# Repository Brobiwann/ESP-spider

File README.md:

# ESP-spider

The ESP-Spider is a quadruped robot inspired by the miniKame (https://github.com/JavierIH/miniKame) . Like the miniKame, it uses sinusoidal functions to control servo positions,
but the design and code were developed independently to better learn the process.
Currently, the robot performs three main actions: move forward, turn right, and turn left, with plans to add more functions in the future as I learn.

# Electronics

The robot features a custom PCB (gerber files and KiCad project are in the repository) with:

  - ESP32 module
  - PCA9685 for PWM control of servos
    
Additional components:

  - 8x MG92B servos
  - 3x 18650 cells
  - 3S BMS 40A 12V with balance charging
  - DFR0753 (DC-DC Buck Converter 6–14V to 5V/8A)
  - Adafruit 1.2" 8x8 LED Matrix Backpack
  - 2.1mmx5.5mm DC Power Jack (Female)
  - Mini 5V fan (20mmx10mm)

# 3D Printing

All STL, Soliworks and STEP files are provided in the repository.
The design is optimized for resin printing and also uses 4x 11mm ball bearings to support the robot weight.
The assembly is completed using M3 and M2 bolts and nuts

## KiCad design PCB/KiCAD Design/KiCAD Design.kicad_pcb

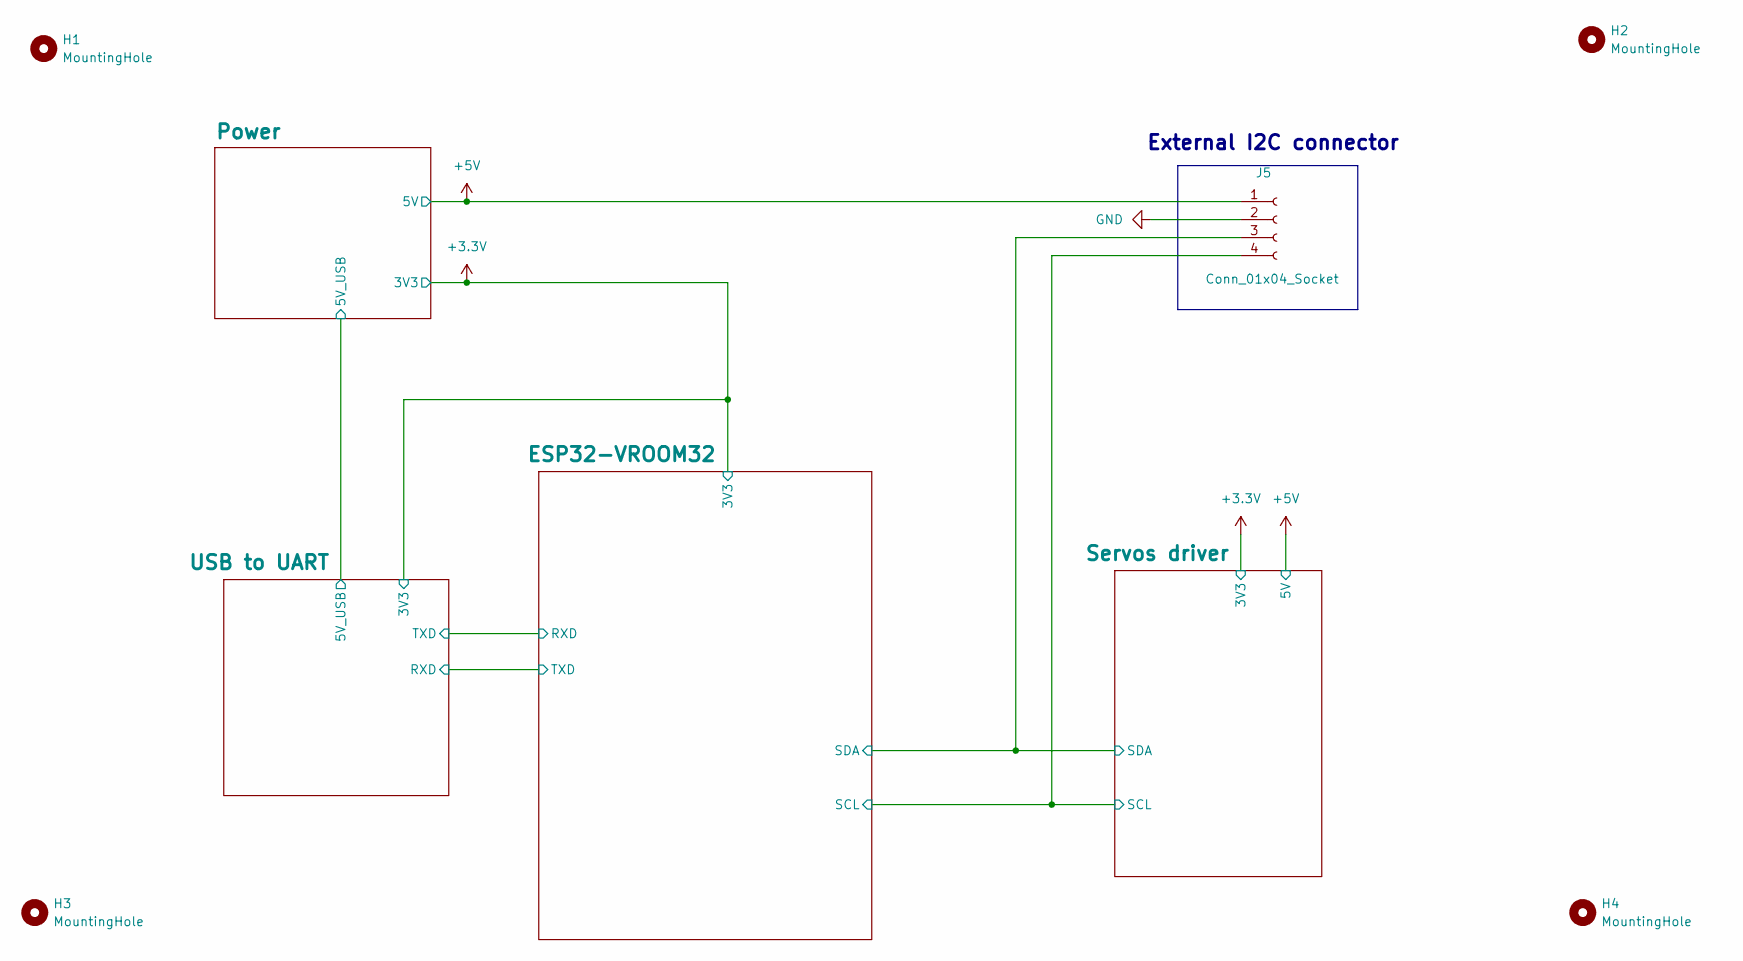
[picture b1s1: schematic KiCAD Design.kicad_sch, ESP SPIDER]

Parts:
H1, H2, H3, H4: MountingHole; MountingHole_2.2mm_M2
J5: Conn_01x04_Socket; JST_PH_B4B-PH-K_1x04_P2.00mm_Vertical; LCSC C131334

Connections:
+5V: J5.1; also elsewhere on the board
/ESP32-VROOM32/SCL: J5.4; also elsewhere on the board
/ESP32-VROOM32/SDA: J5.3; also elsewhere on the board
GND: J5.2; also elsewhere on the board

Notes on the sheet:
External I2C connector

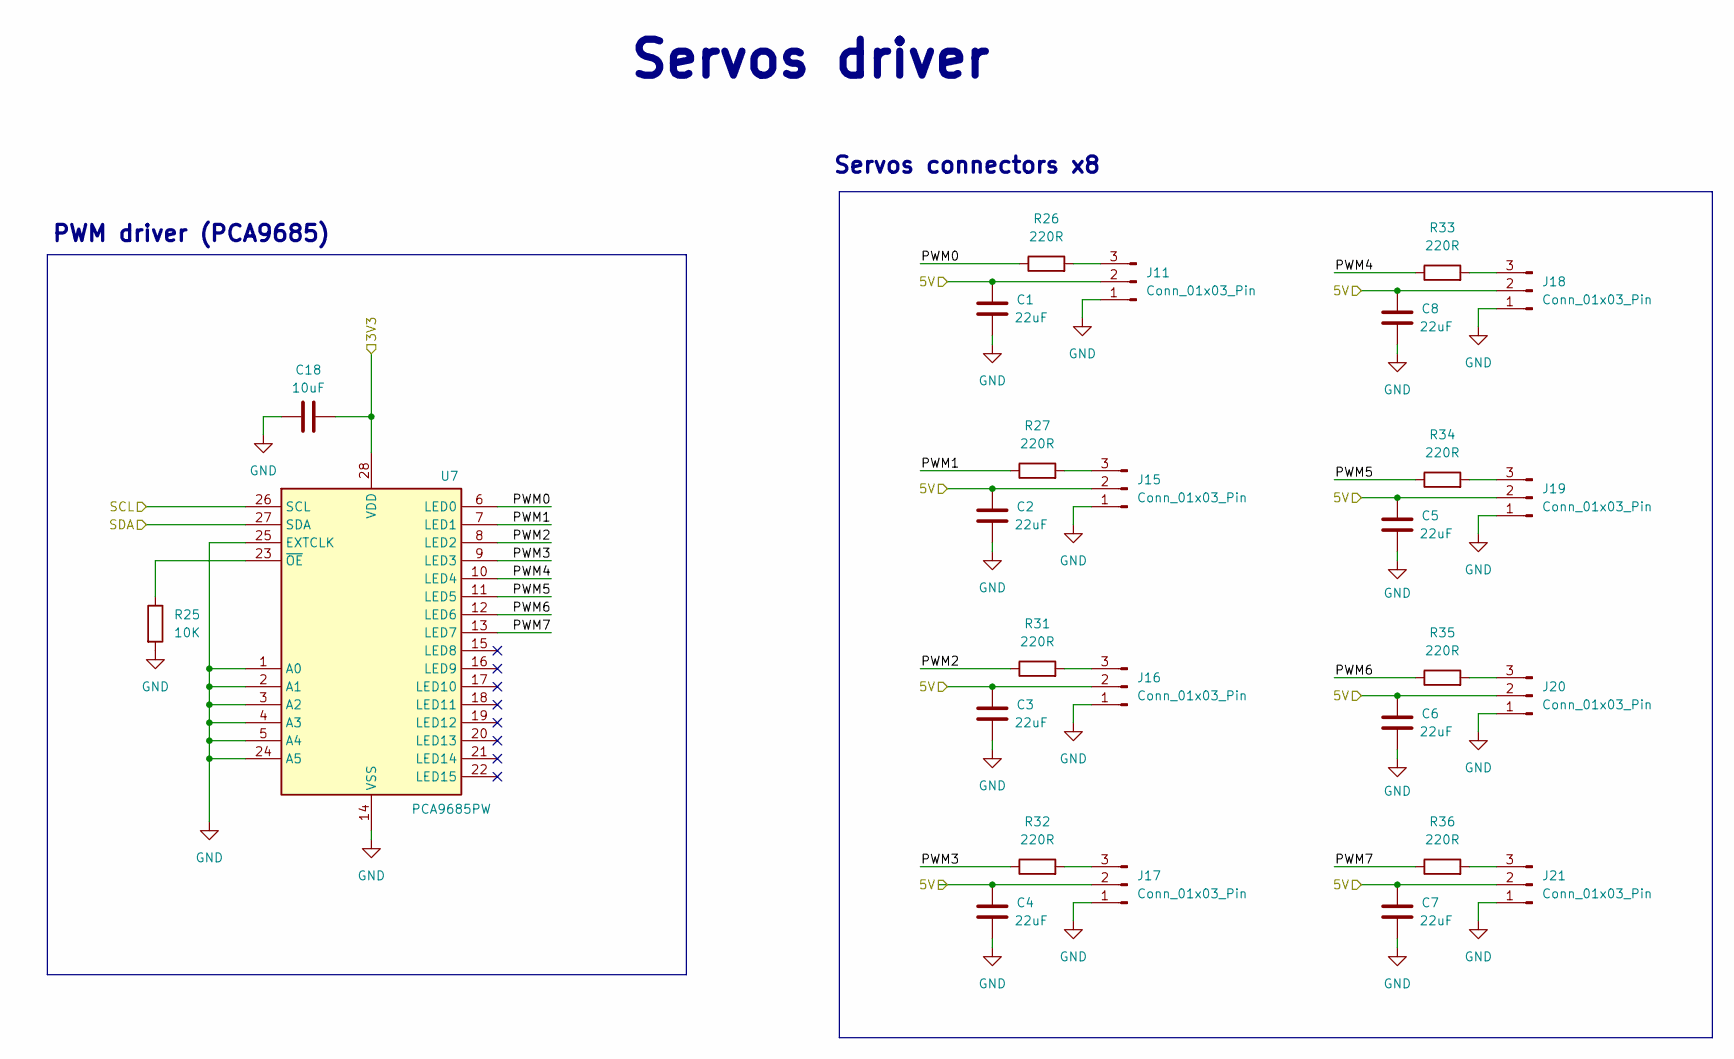
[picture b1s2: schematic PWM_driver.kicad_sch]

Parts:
C1, C2, C3, C4, C5, C6, C7, C8: 22uF; C_0603_1608Metric; LCSC C59461
C18: 10uF; C_0603_1608Metric_Pad1.08x0.95mm_HandSolder; LCSC C19702
J11, J15, J16, J17, J18, J19, J20, J21: Conn_01x03_Pin; PinHeader_1x03_P2.54mm_Vertical
R25: 10K; R_0603_1608Metric_Pad0.98x0.95mm_HandSolder; LCSC C25804
R26, R27, R31, R32, R33, R34, R35, R36: 220R; R_0603_1608Metric_Pad0.98x0.95mm_HandSolder; LCSC C22962
U7: PCA9685PW; TSSOP-28_4.4x9.7mm_P0.65mm; LCSC C2678753

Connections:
+3.3V: C18.1, U7.28 (VDD); also elsewhere on the board
+5V: C1.2, C2.2, C3.2, C4.2, C5.2, C6.2, C7.2, C8.2, J11.2, J15.2, J16.2, J17.2, J18.2, J19.2, J20.2, J21.2; also elsewhere on the board
/ESP32-VROOM32/SCL: U7.26 (SCL); also elsewhere on the board
/ESP32-VROOM32/SDA: U7.27 (SDA); also elsewhere on the board
/Servos driver/PWM0: R26.1, U7.6 (LED0)
/Servos driver/PWM1: R27.1, U7.7 (LED1)
/Servos driver/PWM2: R31.1, U7.8 (LED2)
/Servos driver/PWM3: R32.1, U7.9 (LED3)
/Servos driver/PWM4: R33.1, U7.10 (LED4)
/Servos driver/PWM5: R34.1, U7.11 (LED5)
/Servos driver/PWM6: R35.1, U7.12 (LED6)
/Servos driver/PWM7: R36.1, U7.13 (LED7)
GND: C1.1, C2.1, C3.1, C4.1, C5.1, C6.1, C7.1, C8.1, C18.2, J11.1, J15.1, J16.1, J17.1, J18.1, J19.1, J20.1, J21.1, R25.2, U7.1 (A0), U7.2 (A1), U7.3 (A2), U7.4 (A3), U7.5 (A4), U7.14 (VSS), U7.24 (A5), U7.25 (EXTCLK); also elsewhere on the board
unnamed: J11.3, R26.2
unnamed: J15.3, R27.2
unnamed: J16.3, R31.2
unnamed: J17.3, R32.2
unnamed: J18.3, R33.2
unnamed: J19.3, R34.2
unnamed: J20.3, R35.2
unnamed: J21.3, R36.2
unnamed: R25.1, U7.23 (~OE)

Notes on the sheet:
Servos driver
Servos connectors x8
PWM driver (PCA9685)

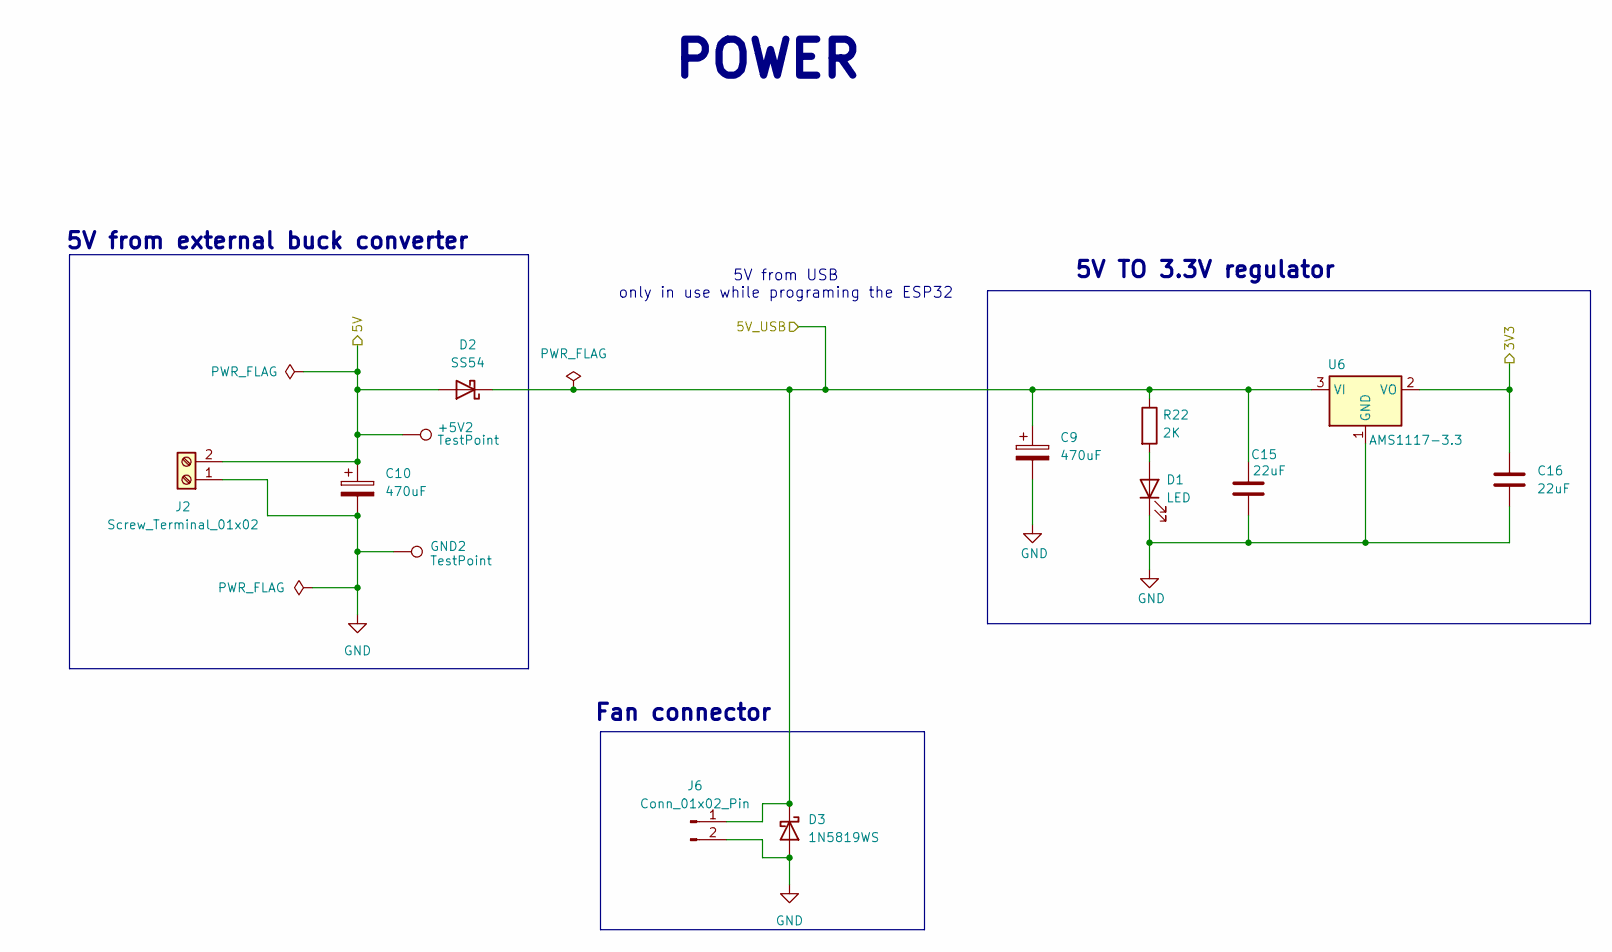
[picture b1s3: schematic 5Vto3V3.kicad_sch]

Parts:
+5V2: TestPoint; TestPoint_Pad_D1.5mm
C9, C10: 470uF; CP_Radial_D8.0mm_P3.50mm
C15, C16: 22uF; C_0603_1608Metric; LCSC C59461
D1: LED; LED_0603_1608Metric_Pad1.05x0.95mm_HandSolder; LCSC C2286
D2: SS54; D_SMA; LCSC C22452
D3: 1N5819WS; D_SOD-323; LCSC C191023
GND2: TestPoint; TestPoint_Pad_D1.5mm
J2: Screw_Terminal_01x02; TerminalBlock_Phoenix_PT-1,5-2-3.5-H_1x02_P3.50mm_Horizontal
J6: Conn_01x02_Pin; JST_PH_B2B-PH-K_1x02_P2.00mm_Vertical
R22: 2K; R_0603_1608Metric_Pad0.98x0.95mm_HandSolder; LCSC C22975
U6: AMS1117-3.3; SOT-223-3_TabPin2; LCSC C6186

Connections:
+3.3V: C16.1, U6.2 (VO); also elsewhere on the board
+5V: +5V2.1, C10.1, D2.2 (A), J2.2; also elsewhere on the board
/Power/5V_USB: C9.1, C15.1, D2.1 (K), D3.1 (K), J6.1, R22.1, U6.3 (VI); also elsewhere on the board
GND: C9.2, C10.2, C15.2, C16.2, D1.1 (K), D3.2 (A), GND2.1, J2.1, J6.2, U6.1 (GND); also elsewhere on the board
unnamed: D1.2 (A), R22.2

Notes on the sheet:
Fan connector
POWER
5V from USB only in use while programing the ESP32
5V from external buck converter
5V TO 3.3V regulator

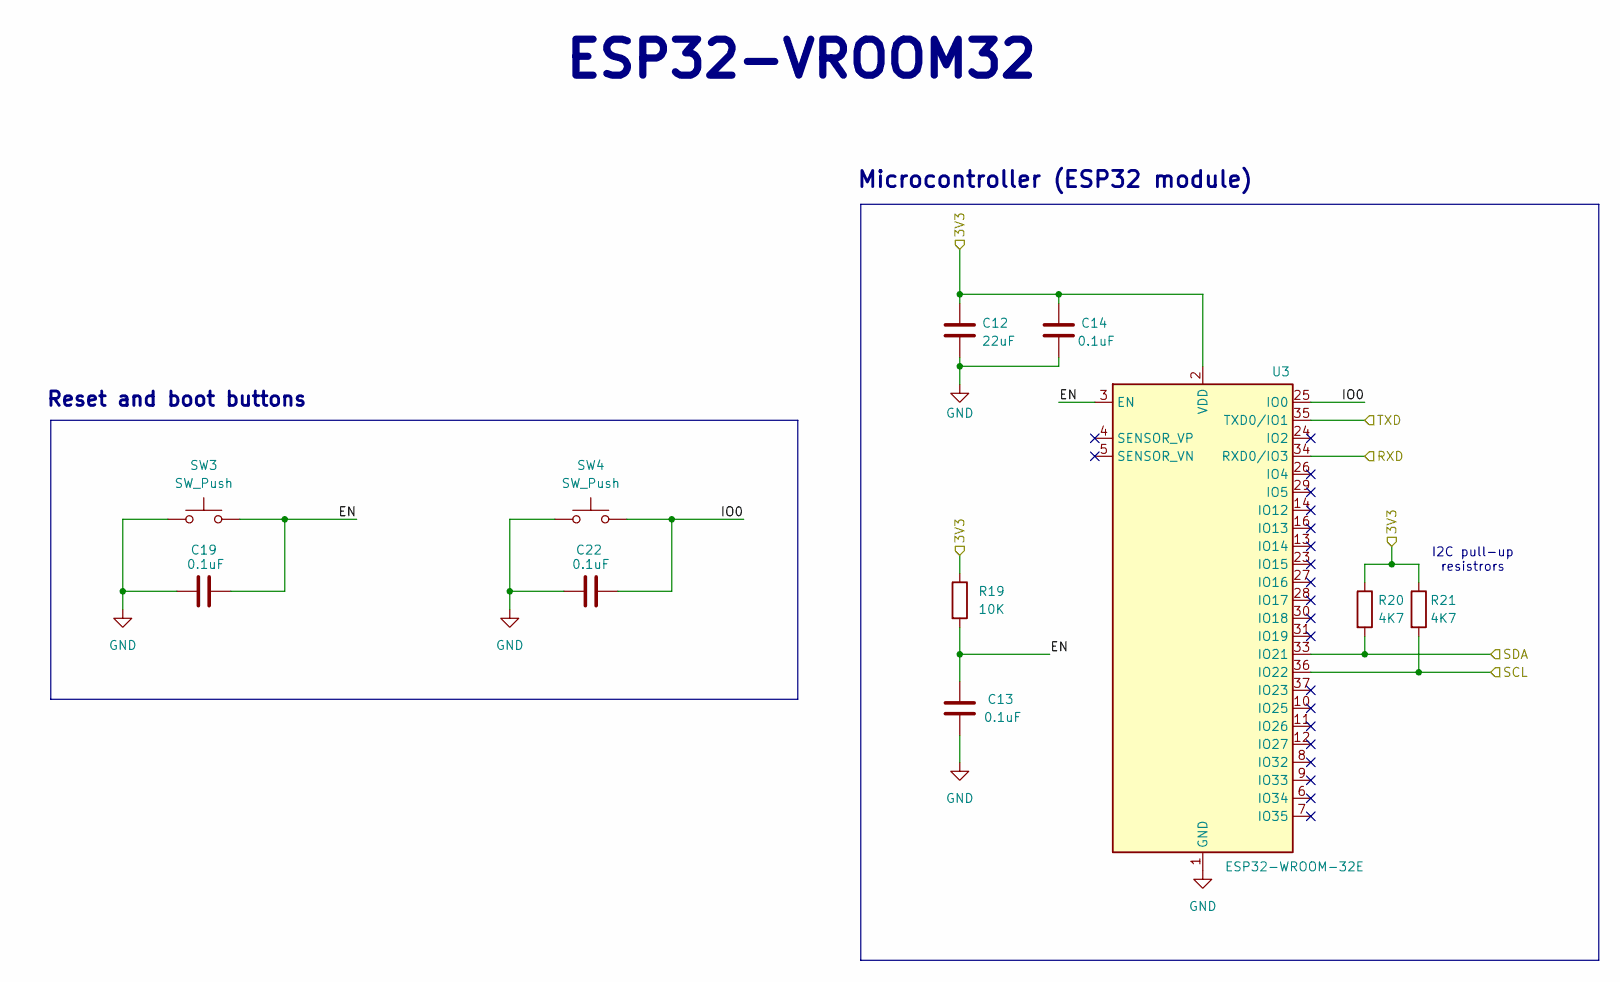
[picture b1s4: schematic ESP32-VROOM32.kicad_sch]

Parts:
C12: 22uF; C_0603_1608Metric; LCSC C59461
C13, C14, C19, C22: 0.1uF; C_0603_1608Metric_Pad1.08x0.95mm_HandSolder; LCSC C14663
R19: 10K; R_0603_1608Metric_Pad0.98x0.95mm_HandSolder; LCSC C25804
R20, R21: 4K7; R_0603_1608Metric_Pad0.98x0.95mm_HandSolder; LCSC C23162
SW3, SW4: SW_Push; SW_Push_1P1T_NO_6x6mm_H9.5mm; LCSC C255812
U3: ESP32-WROOM-32E; ESP32-WROOM-32D; LCSC C701342

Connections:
+3.3V: C12.1, C14.1, R19.1, R20.1, R21.1, U3.2 (VDD); also elsewhere on the board
/ESP32-VROOM32/EN: C13.1, C19.1, R19.2, SW3.2, U3.3 (EN)
/ESP32-VROOM32/IO0: C22.1, SW4.2, U3.25 (IO0)
/ESP32-VROOM32/RXD: U3.34 (RXD0/IO3); also elsewhere on the board
/ESP32-VROOM32/SCL: R21.2, U3.36 (IO22); also elsewhere on the board
/ESP32-VROOM32/SDA: R20.2, U3.33 (IO21); also elsewhere on the board
/ESP32-VROOM32/TXD: U3.35 (TXD0/IO1); also elsewhere on the board
GND: C12.2, C13.2, C14.2, C19.2, C22.2, SW3.1, SW4.1, U3.1 (GND), U3.15 (GND), U3.38 (GND), U3.39 (GND); also elsewhere on the board

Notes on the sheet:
Microcontroller (ESP32 module)
ESP32-VROOM32
Reset and boot buttons
I2C pull-up resistrors

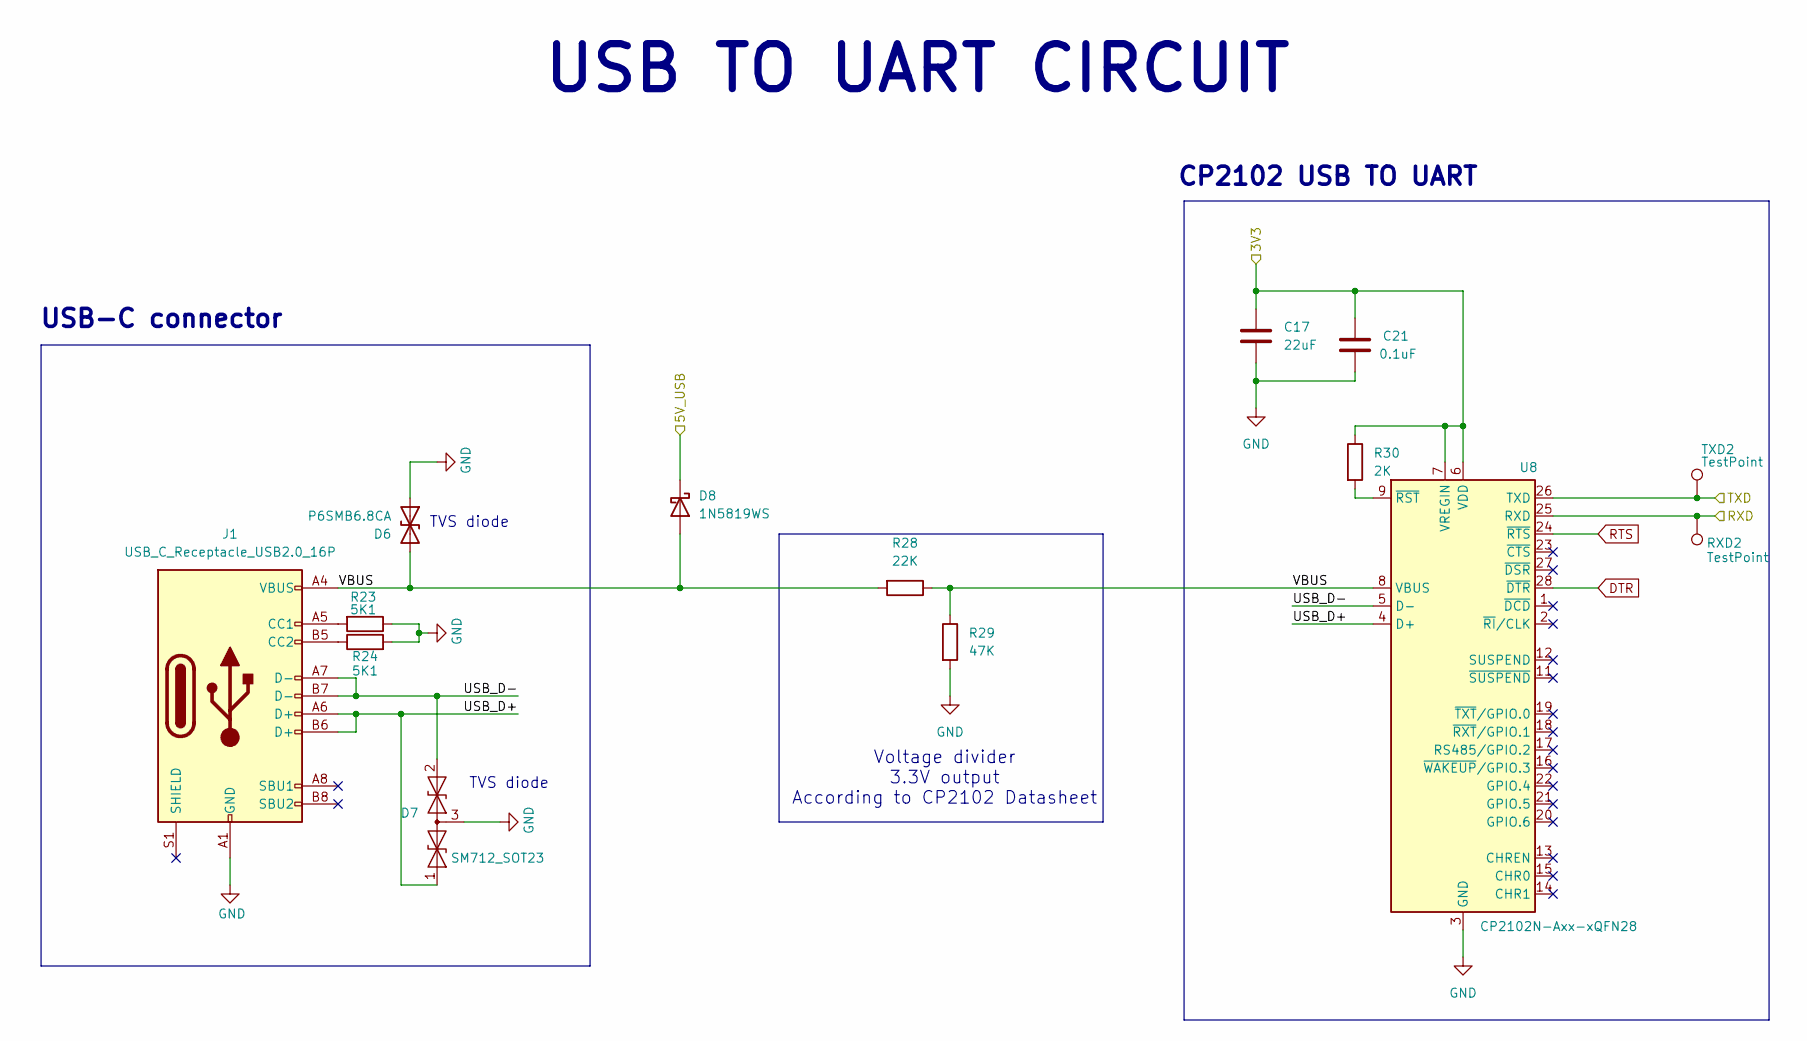
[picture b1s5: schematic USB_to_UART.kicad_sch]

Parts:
C17: 22uF; C_0603_1608Metric; LCSC C59461
C21: 0.1uF; C_0603_1608Metric_Pad1.08x0.95mm_HandSolder; LCSC C14663
D6: P6SMB6.8CA; D_SMB; LCSC C78395
D7: SM712_SOT23; SOT-23; LCSC C32677
D8: 1N5819WS; D_SOD-323; LCSC C191023
J1: USB_C_Receptacle_USB2.0_16P; USB_C_Receptacle_G-Switch_GT-USB-7010ASV; LCSC C2988369
R23, R24: 5K1; R_0603_1608Metric; LCSC C23186
R28: 22K; R_0603_1608Metric_Pad0.98x0.95mm_HandSolder; LCSC C31850
R29: 47K; R_0603_1608Metric_Pad0.98x0.95mm_HandSolder; LCSC C25819
R30: 2K; R_0603_1608Metric_Pad0.98x0.95mm_HandSolder; LCSC C22975
RXD2: TestPoint; TestPoint_Pad_D1.5mm
TXD2: TestPoint; TestPoint_Pad_D1.5mm
U8: CP2102N-Axx-xQFN28; QFN-28-1EP_5x5mm_P0.5mm_EP3.1x3.1mm; LCSC C6568

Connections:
+3.3V: C17.1, C21.1, R30.1, U8.6 (VDD), U8.7 (VREGIN); also elsewhere on the board
/ESP32-VROOM32/RXD: TXD2.1, U8.26 (TXD); also elsewhere on the board
/ESP32-VROOM32/TXD: RXD2.1, U8.25 (RXD); also elsewhere on the board
/Power/5V_USB: D8.1 (K); also elsewhere on the board
/USB to UART/USB_D+: D7.1 (A1), J1.A6 (D+), J1.B6 (D+), U8.4 (D+)
/USB to UART/USB_D-: D7.2 (A2), J1.A7 (D-), J1.B7 (D-), U8.5 (D-)
/USB to UART/VBUS: D6.2 (A2), D8.2 (A), J1.A4 (VBUS), J1.A9 (VBUS), J1.B4 (VBUS), J1.B9 (VBUS), R28.1, R28.2, R29.1, U8.8 (VBUS)
DTR: U8.28 (~DTR)
GND: C17.2, C21.2, D6.1 (A1), D7.3 (common), J1.A1 (GND), J1.A12 (GND), J1.B1 (GND), J1.B12 (GND), R23.1, R24.2, R29.2, U8.3 (GND), U8.29 (GND); also elsewhere on the board
unnamed: J1.A5 (CC1), R23.2
unnamed: J1.B5 (CC2), R24.1
unnamed: R30.2, U8.9 (~RST)
RTS: U8.24 (~RTS)

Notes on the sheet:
CP2102 USB TO UART
TVS diode
Voltage divider 3.3V output According to CP2102 Datasheet
USB TO UART CIRCUIT
USB-C connector

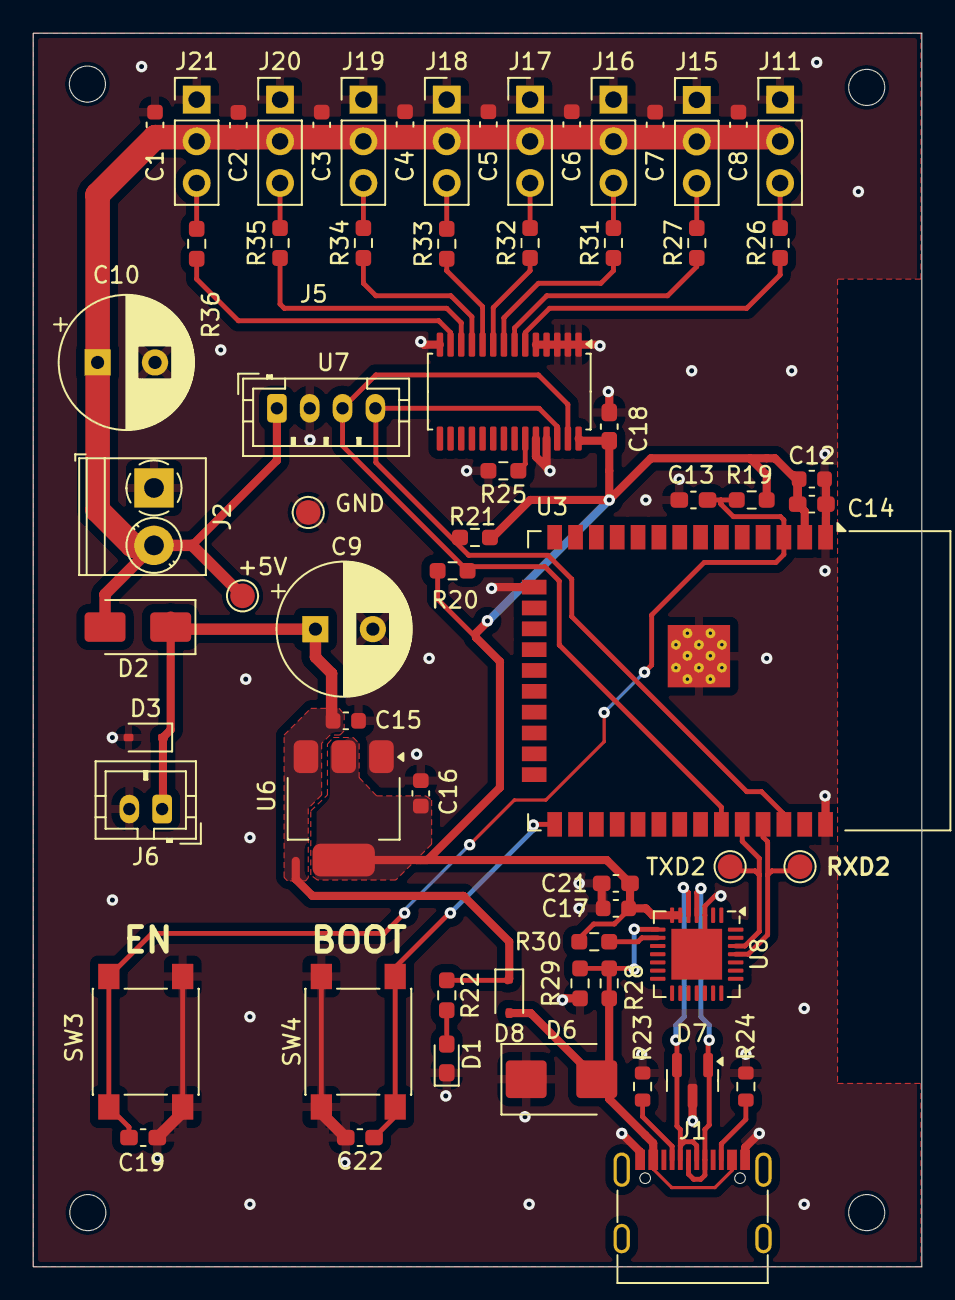
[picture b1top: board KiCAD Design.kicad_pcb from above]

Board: 2 copper layers, 54.2 x 75.2 mm, 70 parts (0 on the bottom side), 34 nets.

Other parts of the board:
+5V: TestPoint; TestPoint_Pad_D1.5mm
GND: TestPoint; TestPoint_Pad_D1.5mm

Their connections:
+5V: +5V.1; also elsewhere on the board
GND: GND.1; also elsewhere on the board

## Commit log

2024-06-15 initial
2024-06-16 Adding PS4 controller
2024-06-16 ps4 controller library
2024-07-07 Added left and right
2024-07-07 removing get pip
2024-11-05 Create Solidworks
2024-11-05 Add led matrix an clean code
